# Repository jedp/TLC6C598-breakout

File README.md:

# TLC6C598 Shift register / LED driver breakout board

The correct timing can be achieved with SPI polarity=0, phase=0. In CubeMX,
this corresponds to CPOL=Low, CPHA=1 edge.

/CLS can be tied high.

After shifting in data, you have to manually raise and lower a GPIO to act as a
register clock to cause the TLC to transfer that data to the storage registers
for display, which is done on the rising edge of RCK.

Since the high time of the register clock is the same as the serial clock, you
can achieve this by pulling the clock GPIO low before transmitting data and
then pulling it high when you're done.

```
	// Register clock low.
	HAL_GPIO_WritePin(GPIOA, GPIO_RCK, GPIO_PIN_RESET);
	
	// Shift data ...
	HAL_SPI_Transmit(&hspi1, (uint8_t*) data, 1, 1);

	// Register clock high: See the blinkies.
	HAL_GPIO_WritePin(GPIOA, GPIO_RCK, GPIO_PIN_SET);
```

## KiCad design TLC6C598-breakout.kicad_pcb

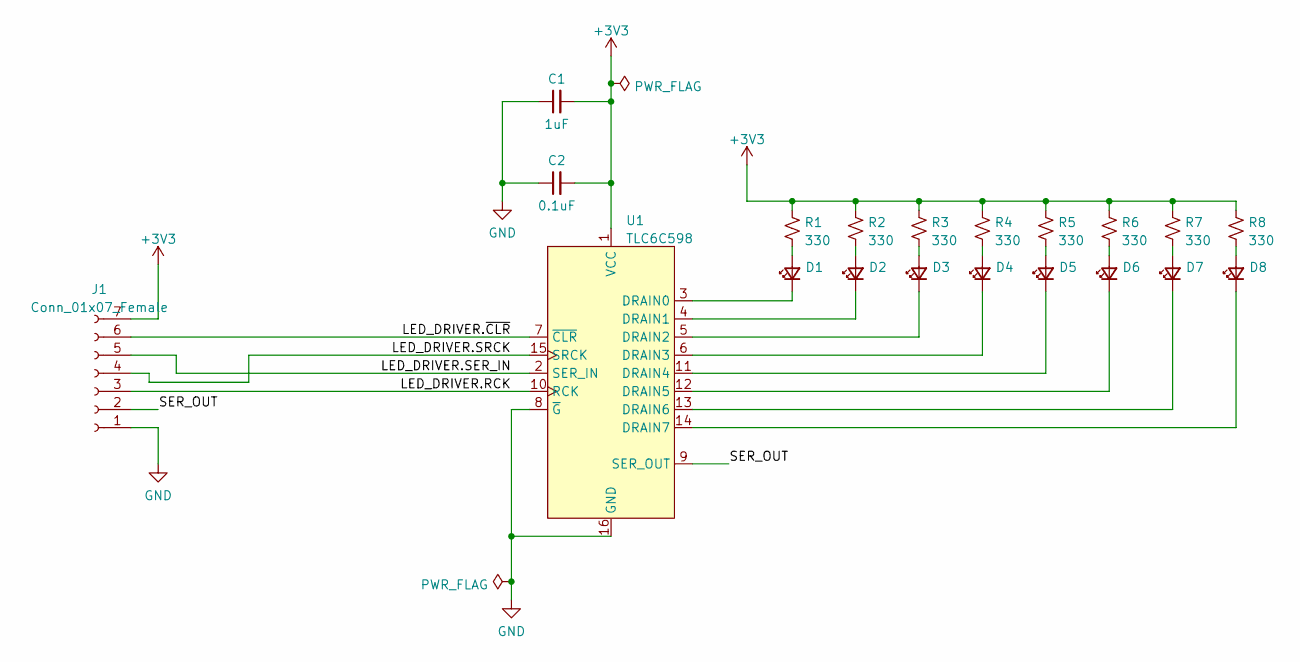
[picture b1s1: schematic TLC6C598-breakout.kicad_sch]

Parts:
C1: 1uF; C_0805_2012Metric
C2: 0.1uF; C_0603_1608Metric
D1, D2, D3, D4, D5, D6, D7, D8: LED_Small; LED_0603_1608Metric
J1: Conn_01x07_Female; PinHeader_1x07_P2.54mm_Vertical
R1, R2, R3, R4, R5, R6, R7, R8: 330; R_0603_1608Metric
U1: TLC6C598; TSSOP-16-1EP_4.4x5mm_P0.65mm_EP3x3mm_ThermalVias

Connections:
+3V3: C1.2, C2.2, J1.7, R1.1, R2.1, R3.1, R4.1, R5.1, R6.1, R7.1, R8.1, U1.1 (VCC)
/LED_DRIVER.RCK: J1.3, U1.10 (RCK)
/LED_DRIVER.SER_IN: J1.5, U1.2 (SER_IN)
/LED_DRIVER.SRCK: J1.4, U1.15 (SRCK)
/LED_DRIVER.~CLR: J1.6, U1.7 (~CLR)
/SER_OUT: J1.2, U1.9 (SER_OUT)
GND: C1.1, C2.1, J1.1, U1.8 (~G), U1.16 (GND)
unnamed: D1.1 (K), U1.3 (DRAIN0)
unnamed: D1.2 (A), R1.2
unnamed: D2.1 (K), U1.4 (DRAIN1)
unnamed: D2.2 (A), R2.2
unnamed: D3.1 (K), U1.5 (DRAIN2)
unnamed: D3.2 (A), R3.2
unnamed: D4.1 (K), U1.6 (DRAIN3)
unnamed: D4.2 (A), R4.2
unnamed: D5.1 (K), U1.11 (DRAIN4)
unnamed: D5.2 (A), R5.2
unnamed: D6.1 (K), U1.12 (DRAIN5)
unnamed: D6.2 (A), R6.2
unnamed: D7.1 (K), U1.13 (DRAIN6)
unnamed: D7.2 (A), R7.2
unnamed: D8.1 (K), U1.14 (DRAIN7)
unnamed: D8.2 (A), R8.2

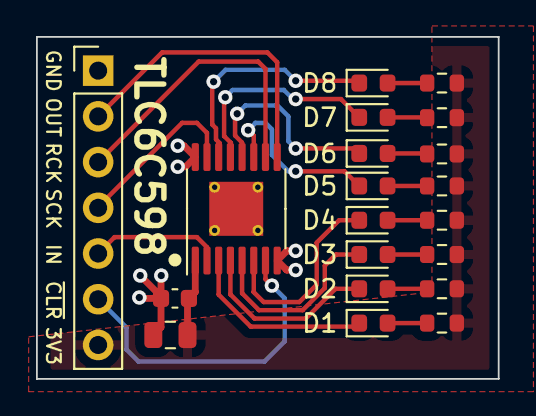
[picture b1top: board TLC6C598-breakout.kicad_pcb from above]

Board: 2 copper layers, 25.7 x 19.0 mm, 20 parts (0 on the bottom side), 23 nets.

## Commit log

2023-12-26 TLC6C598 breakout board
2023-12-26 PCB image
2023-12-31 Document SPI implementation
